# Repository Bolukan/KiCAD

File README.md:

# KiCAD
KiCad projects

## MoistureHub
To process multiple capacitive moisture sensors  
Project date: 2025-04-21  

## P1 Monitor
Multicolor leds to show home energy use  
Project date: 2024-09-29  

## W5500 RPI add-on
Add-on LAN on RPI Zero
Project date: 2024-09-29  

## SensorHub
To process multiple sensors  
Project date: 2023-06-24  

## WLED 12V ESP32
To control christmas lights with WLED  
Project date: 2022-06-07  

## ILI9341  
To combine an ILI9341 and a D1 mini. To be used with a 90 degree angle  
Project date: 2021-09-27  

## Power latching circuit  
Power latching circuit - first pcb design  
Project date: 2020-03-01

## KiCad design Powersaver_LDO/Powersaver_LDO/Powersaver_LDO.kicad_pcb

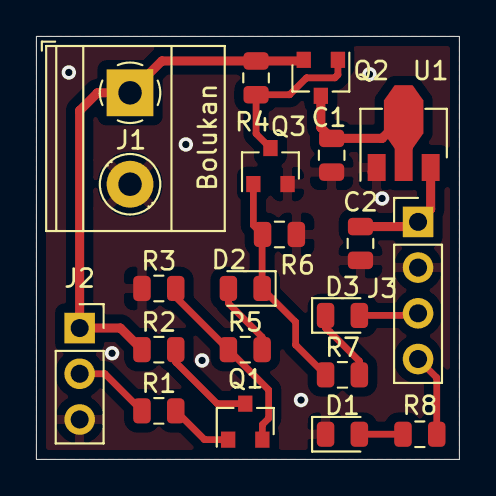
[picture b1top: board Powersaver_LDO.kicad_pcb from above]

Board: 2 copper layers, 23.5 x 23.5 mm, 20 parts (0 on the bottom side), 15 nets.

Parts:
C1, C2: 10µF; C_0805_2012Metric
D1: LED; D_0805_2012Metric
D2, D3: 1N5819W; D_0805_2012Metric
J1: Power Supply; TerminalBlock_Phoenix_MKDS-1,5-2-5.08_1x02_P5.08mm_Horizont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
J2: Trigger; PinSocket_1x03_P2.54mm_Vertical
J3: Microcontroller; PinHeader_1x04_P2.54mm_Vertical
Q1, Q3: 2N3904; SOT-23
Q2: AO3413; SOT-23
R1: 1K; R_0805_2012Metric
R2, R5: 10K; R_0805_2012Metric
R3: 220K; R_0805_2012Metric
R4, R6: 100K; R_0805_2012Metric
R7: 220; R_0805_2012Metric
R8: 330; R_0805_2012Metric
U1: HT73xx-1-SOT89; SOT-89-3

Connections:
/trigger: J2.2, R1.1
GND: C1.2, C2.2, D1.1, J1.2, J2.3, J3.2, Q3.2, R3.2, R6.2, U1.1
unnamed: C1.1, Q2.3, U1.2
unnamed: C2.1, J3.1, U1.3
unnamed: D1.2, R8.2
unnamed: D2.1, Q3.1, R6.1, R7.2
unnamed: D2.2, R5.2
unnamed: D3.1, R7.1
unnamed: D3.2, J3.3
unnamed: J3.4, R8.1
unnamed: Q1.1, R1.2
unnamed: Q1.2, R3.1, R5.1
unnamed: Q1.3, R2.2
unnamed: Q2.1, Q3.3, R4.1
VCC: J1.1, J2.1, Q2.2, R2.1, R4.2

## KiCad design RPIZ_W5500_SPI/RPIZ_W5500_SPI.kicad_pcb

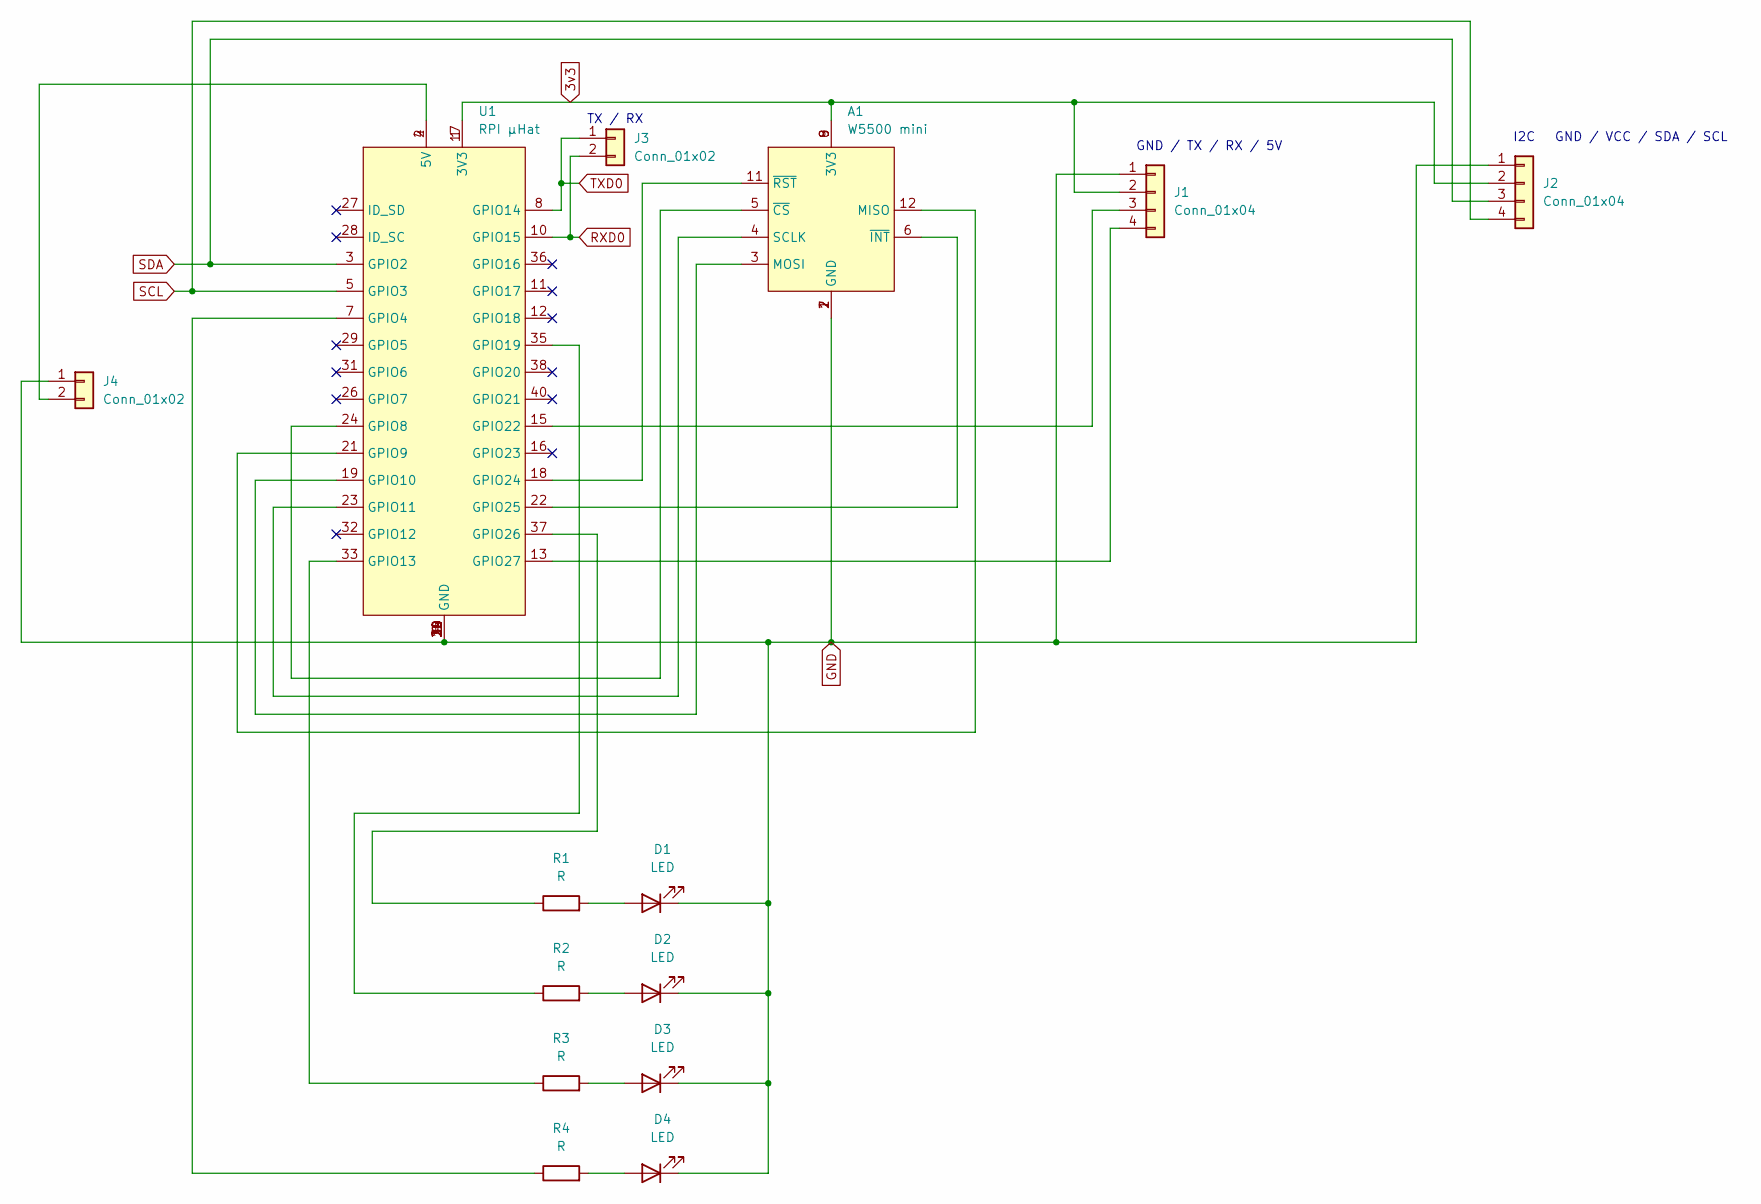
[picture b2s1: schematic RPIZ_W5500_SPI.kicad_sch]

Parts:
A1: W5500 mini; Module_W5500_mini
D1, D2, D3, D4: LED; LED_0805_2012Metric_Pad1.15x1.40mm_HandSolder
J1, J2: Conn_01x04; PinHeader_1x04_P2.54mm_Vertical
J3, J4: Conn_01x02; PinHeader_1x02_P2.54mm_Vertical
R1, R2, R3, R4: R; R_0805_2012Metric_Pad1.20x1.40mm_HandSolder
U1: RPI µHat; RPI µHat 20x2 header

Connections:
3v3: A1.8 (3V3), A1.9 (3V3), J1.2, J2.2, U1.1 (3V3), U1.17 (3V3)
GND: A1.1 (GND), A1.2 (GND), A1.7 (GND), D1.1 (K), D2.1 (K), D3.1 (K), D4.1 (K), J1.1, J2.1, J4.1, U1.6 (GND), U1.9 (GND), U1.14 (GND), U1.20 (GND), U1.25 (GND), U1.30 (GND), U1.34 (GND), U1.39 (GND)
unnamed: A1.12 (MISO), U1.21 (GPIO9)
unnamed: A1.3 (MOSI), U1.19 (GPIO10)
unnamed: A1.4 (SCLK), U1.23 (GPIO11)
unnamed: A1.5 (~CS), U1.24 (GPIO8)
unnamed: A1.6 (~INT), U1.22 (GPIO25)
unnamed: A1.11 (~RST), U1.18 (GPIO24)
unnamed: D1.2 (A), R1.2
unnamed: D2.2 (A), R2.2
unnamed: D3.2 (A), R3.2
unnamed: D4.2 (A), R4.2
unnamed: J1.3, U1.15 (GPIO22)
unnamed: J1.4, U1.13 (GPIO27)
unnamed: J4.2, U1.2 (5V), U1.4 (5V)
unnamed: R4.1, U1.7 (GPIO4)
unnamed: R3.1, U1.33 (GPIO13)
unnamed: R2.1, U1.35 (GPIO19)
unnamed: R1.1, U1.37 (GPIO26)
RXD0: J3.2, U1.10 (GPIO15)
SCL: J2.4, U1.5 (GPIO3)
SDA: J2.3, U1.3 (GPIO2)
TXD0: J3.1, U1.8 (GPIO14)

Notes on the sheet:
GND / TX / RX / 5V
I2C
GND / VCC / SDA / SCL
TX / RX

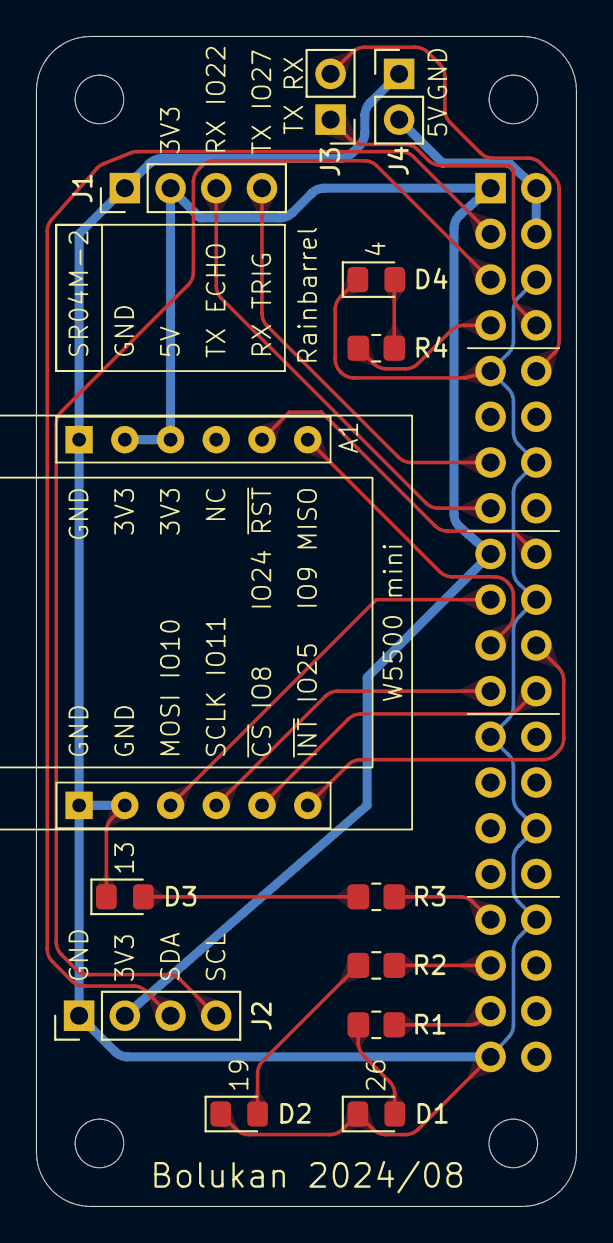
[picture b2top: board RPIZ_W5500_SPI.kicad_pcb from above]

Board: 2 copper layers, 30.0 x 65.0 mm, 14 parts (0 on the bottom side), 23 nets.

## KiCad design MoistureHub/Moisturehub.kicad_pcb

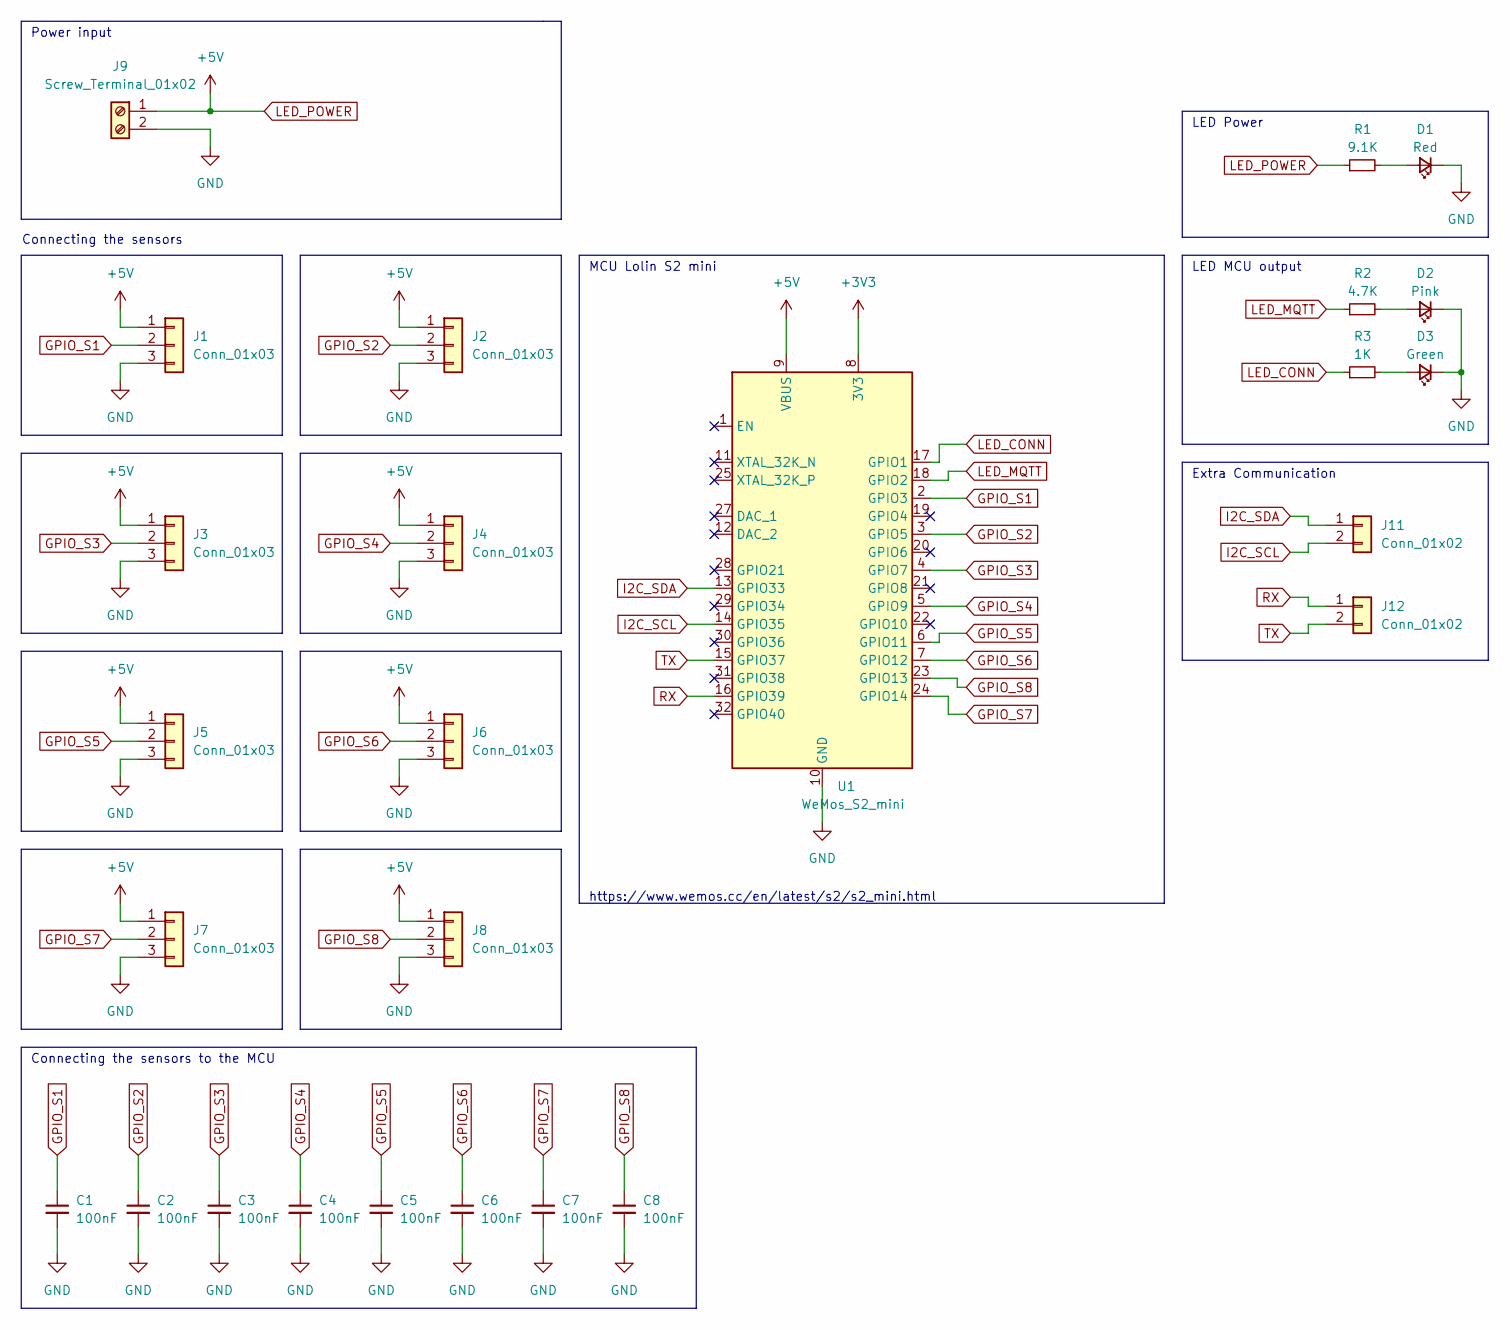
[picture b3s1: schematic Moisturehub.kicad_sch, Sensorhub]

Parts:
C1, C2, C3, C4, C5, C6, C7, C8: 100nF; C_1206_3216Metric_Pad1.33x1.80mm_HandSolder
D1: Red; LED_1206_3216Metric_Pad1.42x1.75mm_HandSolder
D2: Pink; LED_1206_3216Metric_Pad1.42x1.75mm_HandSolder
D3: Green; LED_1206_3216Metric_Pad1.42x1.75mm_HandSolder
J1, J2, J3, J4, J5, J6, J7, J8: Conn_01x03; JST_XH_S3B-XH-A_1x03_P2.50mm_Horizontal
J9: Screw_Terminal_01x02; TerminalBlock_Phoenix_MKDS-1,5-2-5.08_1x02_P5.08mm_Horizont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
J11, J12: Conn_01x02; PinHeader_1x02_P2.54mm_Vertical
R1: 9.1K; R_1206_3216Metric_Pad1.30x1.75mm_HandSolder
R2: 4.7K; R_1206_3216Metric_Pad1.30x1.75mm_HandSolder
R3: 1K; R_1206_3216Metric_Pad1.30x1.75mm_HandSolder
U1: WeMos_S2_mini; WEMOS_S2_mini

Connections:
+3V3: U1.8 (3V3)
GND: C1.2, C2.2, C3.2, C4.2, C5.2, C6.2, C7.2, C8.2, D1.1 (K), D2.1 (K), D3.1 (K), J1.3, J2.3, J3.3, J4.3, J5.3, J6.3, J7.3, J8.3, J9.2, U1.10 (GND), U1.26 (GND)
GPIO_S1: C1.1, J1.2, U1.2 (GPIO3)
GPIO_S2: C2.1, J2.2, U1.3 (GPIO5)
GPIO_S3: C3.1, J3.2, U1.4 (GPIO7)
GPIO_S4: C4.1, J4.2, U1.5 (GPIO9)
GPIO_S5: C5.1, J5.2, U1.6 (GPIO11)
GPIO_S6: C6.1, J6.2, U1.7 (GPIO12)
GPIO_S7: C7.1, J7.2, U1.24 (GPIO14)
GPIO_S8: C8.1, J8.2, U1.23 (GPIO13)
I2C_SCL: J11.2, U1.14 (GPIO35)
I2C_SDA: J11.1, U1.13 (GPIO33)
LED_CONN: R3.1, U1.17 (GPIO1)
LED_MQTT: R2.1, U1.18 (GPIO2)
LED_POWER: J1.1, J2.1, J3.1, J4.1, J5.1, J6.1, J7.1, J8.1, J9.1, R1.1, U1.9 (VBUS)
unnamed: D1.2 (A), R1.2
unnamed: D2.2 (A), R2.2
unnamed: D3.2 (A), R3.2
RX: J12.1, U1.16 (GPIO39)
TX: J12.2, U1.15 (GPIO37)

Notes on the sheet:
Extra Communication
Connecting the sensors to the MCU
LED Power
Power input
https://www.wemos.cc/en/latest/s2/s2_mini.html
Connecting the sensors
MCU Lolin S2 mini
LED MCU output

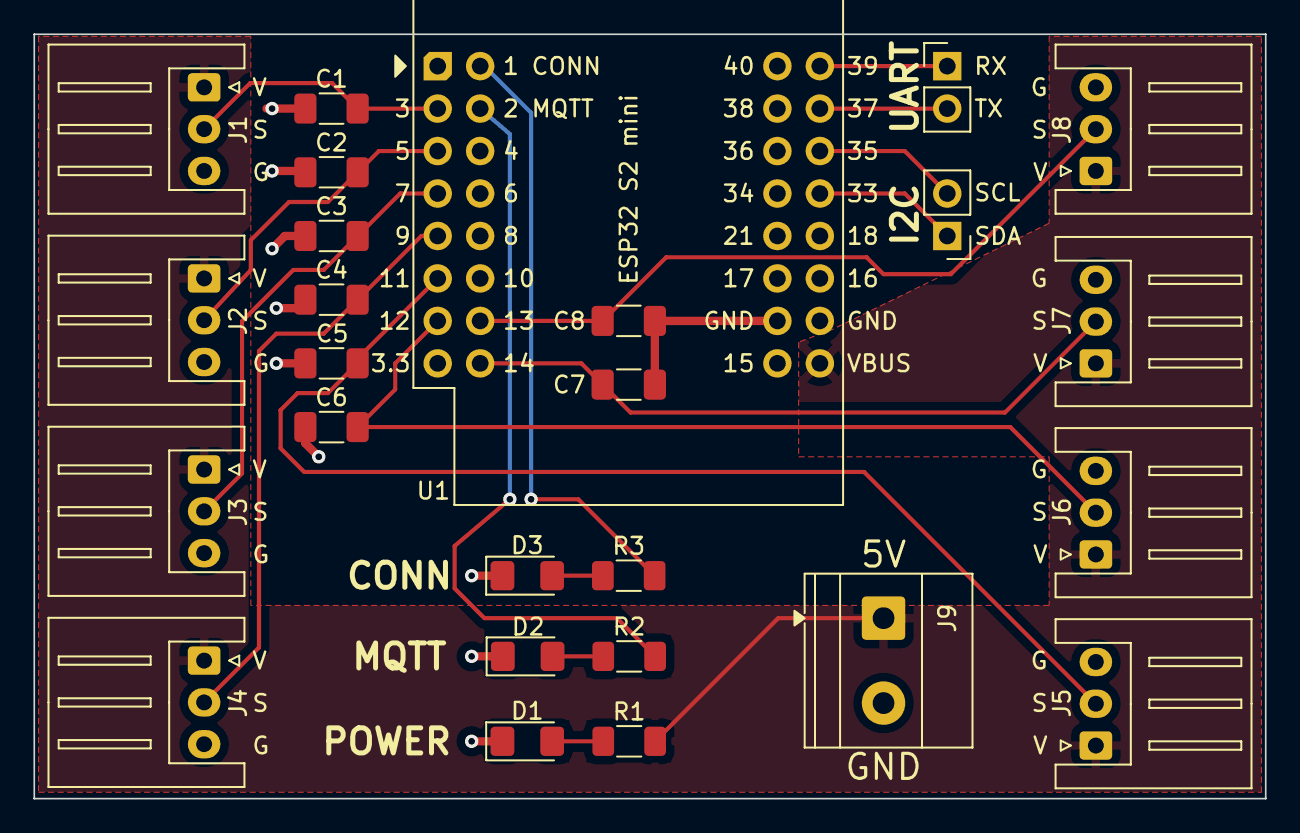
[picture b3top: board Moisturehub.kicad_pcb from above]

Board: 2 copper layers, 73.7 x 45.7 mm, 26 parts (0 on the bottom side), 19 nets.

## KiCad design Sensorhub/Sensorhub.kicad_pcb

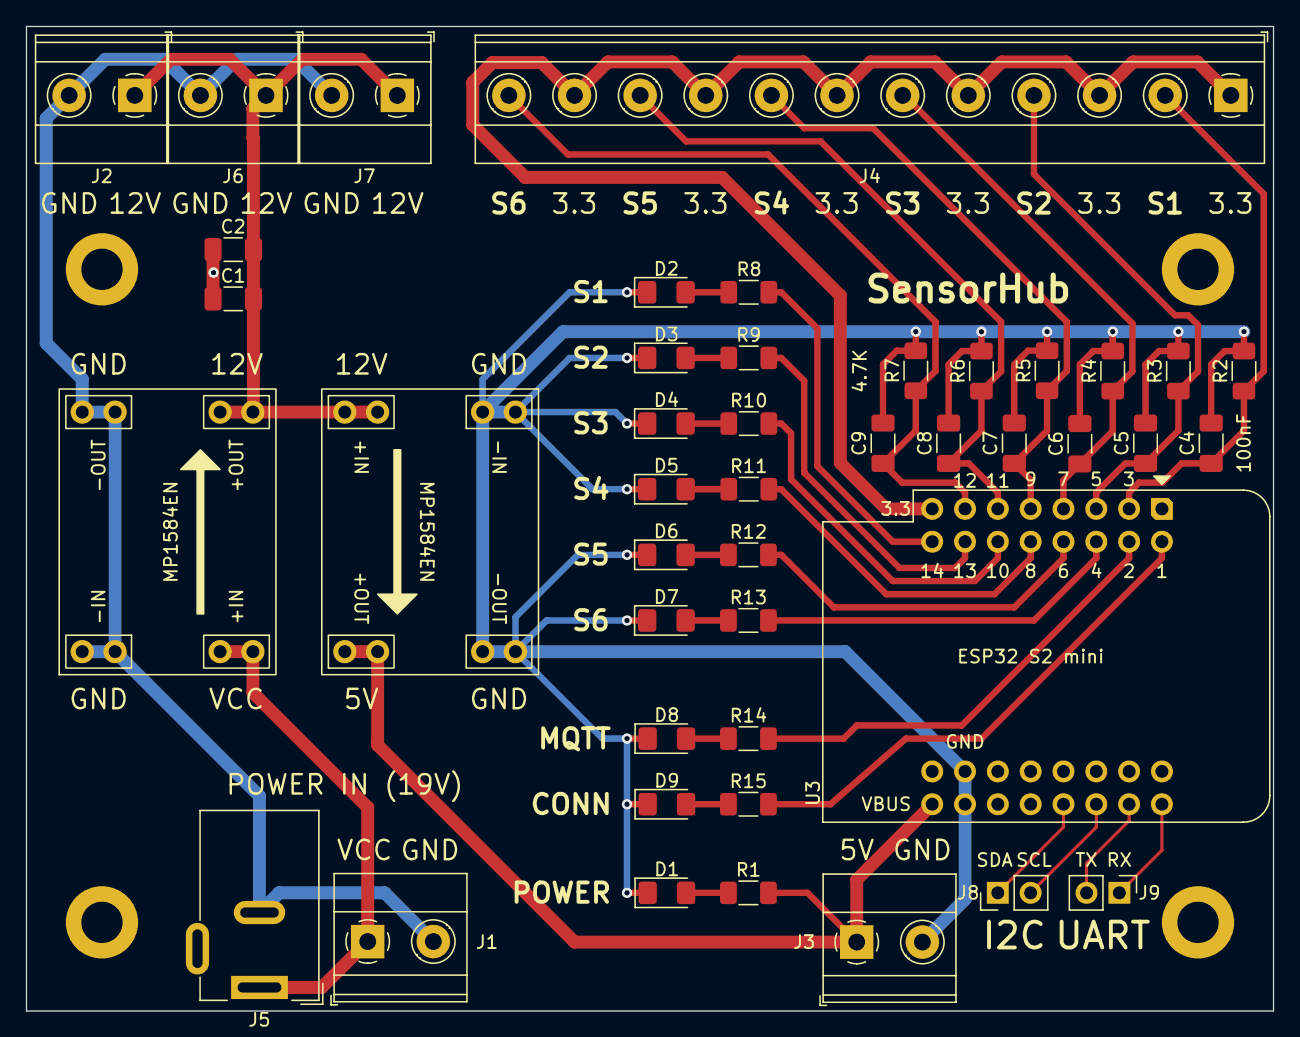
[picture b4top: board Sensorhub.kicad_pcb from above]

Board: 2 copper layers, 96.5 x 76.2 mm, 48 parts (0 on the bottom side), 32 nets.

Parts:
C1, C2, C4, C5, C6, C7, C8, C9: 100nF; C_1206_3216Metric_Pad1.33x1.80mm_HandSolder
D1: Red; LED_1206_3216Metric_Pad1.42x1.75mm_HandSolder
D2, D3, D4, D5, D6, D7: Blue; LED_1206_3216Metric_Pad1.42x1.75mm_HandSolder
D8, D9: Pink; LED_1206_3216Metric_Pad1.42x1.75mm_HandSolder
H1, H2, H3, H4: MountingHole; MountingHole_3.2mm_M3_DIN965_Pad
J1, J2, J3, J6, J7: Screw_Terminal_01x02; TerminalBlock_Phoenix_MKDS-1,5-2-5.08_1x02_P5.08mm_Horizont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
J4: Screw_Terminal_01x12; TerminalBlock_Phoenix_MKDS-1,5-12-5.08_1x12_P5.08mm_Horizon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
J5: Barrel_Jack; BarrelJack_Wuerth_6941xx301002
J8, J9: Conn_01x02; PinHeader_1x02_P2.54mm_Vertical
R1, R8, R9, R10, R11, R12, R13, R14, R15: 1K; R_1206_3216Metric_Pad1.30x1.75mm_HandSolder
R2, R3, R4, R5, R6, R7: 4.7K; R_1206_3216Metric_Pad1.30x1.75mm_HandSolder
U1: MP1584EN-12V; MP1584EN_PCB
U2: MP1584EN-5V; MP1584EN_PCB
U3: WeMos_S2_mini; WEMOS_S2_mini

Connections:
+3V3: J4.1, J4.3, J4.5, J4.7, J4.9, J4.11, U3.8 (3V3)
+5V: J3.1, R1.1, U2.4 (OUT+), U3.9 (VBUS)
+12V: C1.1, C2.1, J2.1, J6.1, J7.1, U1.4 (OUT+), U2.2 (IN+)
GND: C1.2, C2.2, C4.2, C5.2, C6.2, C7.2, C8.2, C9.2, D1.1 (K), D2.1 (K), D3.1 (K), D4.1 (K), D5.1 (K), D6.1 (K), D7.1 (K), D8.1 (K), D9.1 (K), J1.2, J2.2, J3.2, J5.2, J6.2, J7.2, R2.2, R3.2, R4.2, R5.2, R6.2, R7.2, U1.1 (IN-), U1.3 (OUT-), U2.1 (IN-), U2.3 (OUT-), U3.10 (GND), U3.26 (GND)
GPIO_LED1: R8.1, U3.24 (GPIO14)
GPIO_LED2: R9.1, U3.23 (GPIO13)
GPIO_LED3: R10.1, U3.22 (GPIO10)
GPIO_LED4: R11.1, U3.21 (GPIO8)
GPIO_LED5: R12.1, U3.20 (GPIO6)
GPIO_LED6: R13.1, U3.19 (GPIO4)
GPIO_LED_B: R15.1, U3.17 (GPIO1)
GPIO_LED_MQTT: R14.1, U3.18 (GPIO2)
GPIO_S1: C4.1, J4.2, R2.1, U3.2 (GPIO3)
GPIO_S2: C5.1, J4.4, R3.1, U3.3 (GPIO5)
GPIO_S3: C6.1, J4.6, R4.1, U3.4 (GPIO7)
GPIO_S4: C7.1, J4.8, R5.1, U3.5 (GPIO9)
GPIO_S5: C8.1, J4.10, R6.1, U3.6 (GPIO11)
GPIO_S6: C9.1, J4.12, R7.1, U3.7 (GPIO12)
I2C_SCL: J8.2, U3.14 (GPIO35)
I2C_SDA: J8.1, U3.13 (GPIO33)
unnamed: D1.2 (A), R1.2
unnamed: D2.2 (A), R8.2
unnamed: D3.2 (A), R9.2
unnamed: D4.2 (A), R10.2
unnamed: D5.2 (A), R11.2
unnamed: D6.2 (A), R12.2
unnamed: D7.2 (A), R13.2
unnamed: D8.2 (A), R14.2
unnamed: D9.2 (A), R15.2
RX: J9.1, U3.16 (GPIO39)
TX: J9.2, U3.15 (GPIO37)
VCC: J1.1, J5.1, U1.2 (IN+)

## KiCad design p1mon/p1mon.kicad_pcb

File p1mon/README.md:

## P1 Monitor
Multicolor leds to show home energy use  
Project date: 2024-09-29

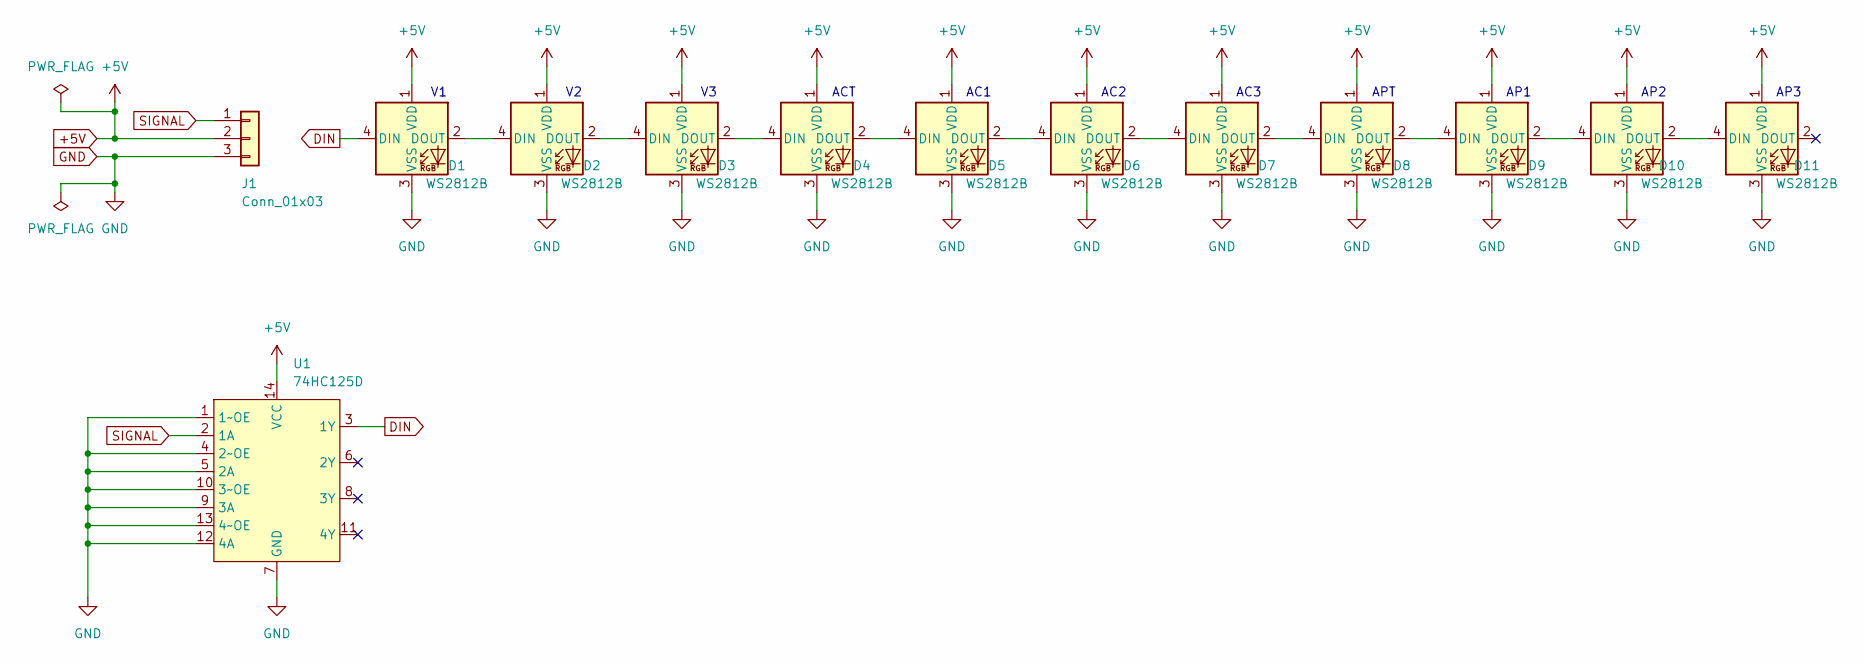
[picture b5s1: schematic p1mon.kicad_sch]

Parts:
D1, D2, D3, D4, D5, D6, D7, D8, D9, D10, D11: WS2812B; LED_WS2812B_PLCC4_5.0x5.0mm_P3.2mm
J1: Conn_01x03; PinHeader_1x03_P2.54mm_Vertical
U1: 74HC125D; SOP-14_3.9x8.65mm_P1.27mm

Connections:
+5V: D1.1 (VDD), D2.1 (VDD), D3.1 (VDD), D4.1 (VDD), D5.1 (VDD), D6.1 (VDD), D7.1 (VDD), D8.1 (VDD), D9.1 (VDD), D10.1 (VDD), D11.1 (VDD), J1.2, U1.14 (VCC)
DIN: D1.4 (DIN), U1.3 (1Y)
GND: D1.3 (VSS), D2.3 (VSS), D3.3 (VSS), D4.3 (VSS), D5.3 (VSS), D6.3 (VSS), D7.3 (VSS), D8.3 (VSS), D9.3 (VSS), D10.3 (VSS), D11.3 (VSS), J1.3, U1.1 (1~OE), U1.4 (2~OE), U1.5 (2A), U1.7 (GND), U1.9 (3A), U1.10 (3~OE), U1.12 (4A), U1.13 (4~OE)
unnamed: D1.2 (DOUT), D2.4 (DIN)
unnamed: D2.2 (DOUT), D3.4 (DIN)
unnamed: D3.2 (DOUT), D4.4 (DIN)
unnamed: D4.2 (DOUT), D5.4 (DIN)
unnamed: D5.2 (DOUT), D6.4 (DIN)
unnamed: D6.2 (DOUT), D7.4 (DIN)
unnamed: D7.2 (DOUT), D8.4 (DIN)
unnamed: D8.2 (DOUT), D9.4 (DIN)
unnamed: D9.2 (DOUT), D10.4 (DIN)
unnamed: D10.2 (DOUT), D11.4 (DIN)
SIGNAL: J1.1, U1.2 (1A)

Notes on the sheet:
AC2
APT
AP1
ACT
AP2
AC3
AP3
AC1

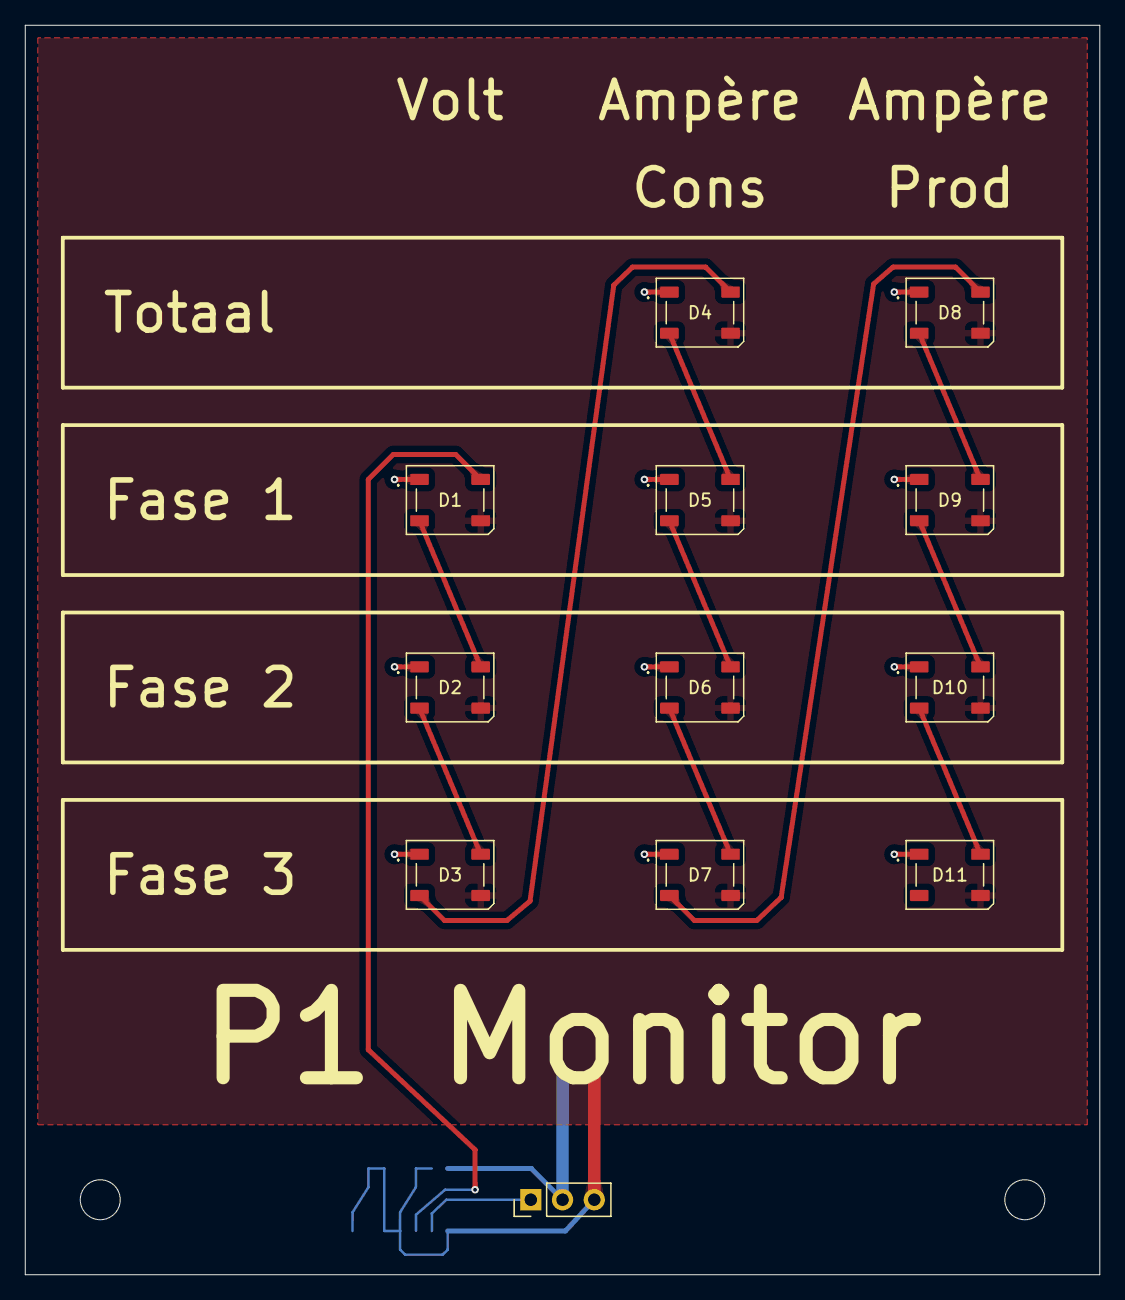
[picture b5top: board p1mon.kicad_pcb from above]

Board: 2 copper layers, 86.0 x 100.0 mm, 13 parts (1 on the bottom side), 14 nets.

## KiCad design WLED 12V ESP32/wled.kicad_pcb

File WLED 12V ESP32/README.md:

## WLED 12V ESP32
To control christmas lights with WLED  
Project date: 2022-06-07

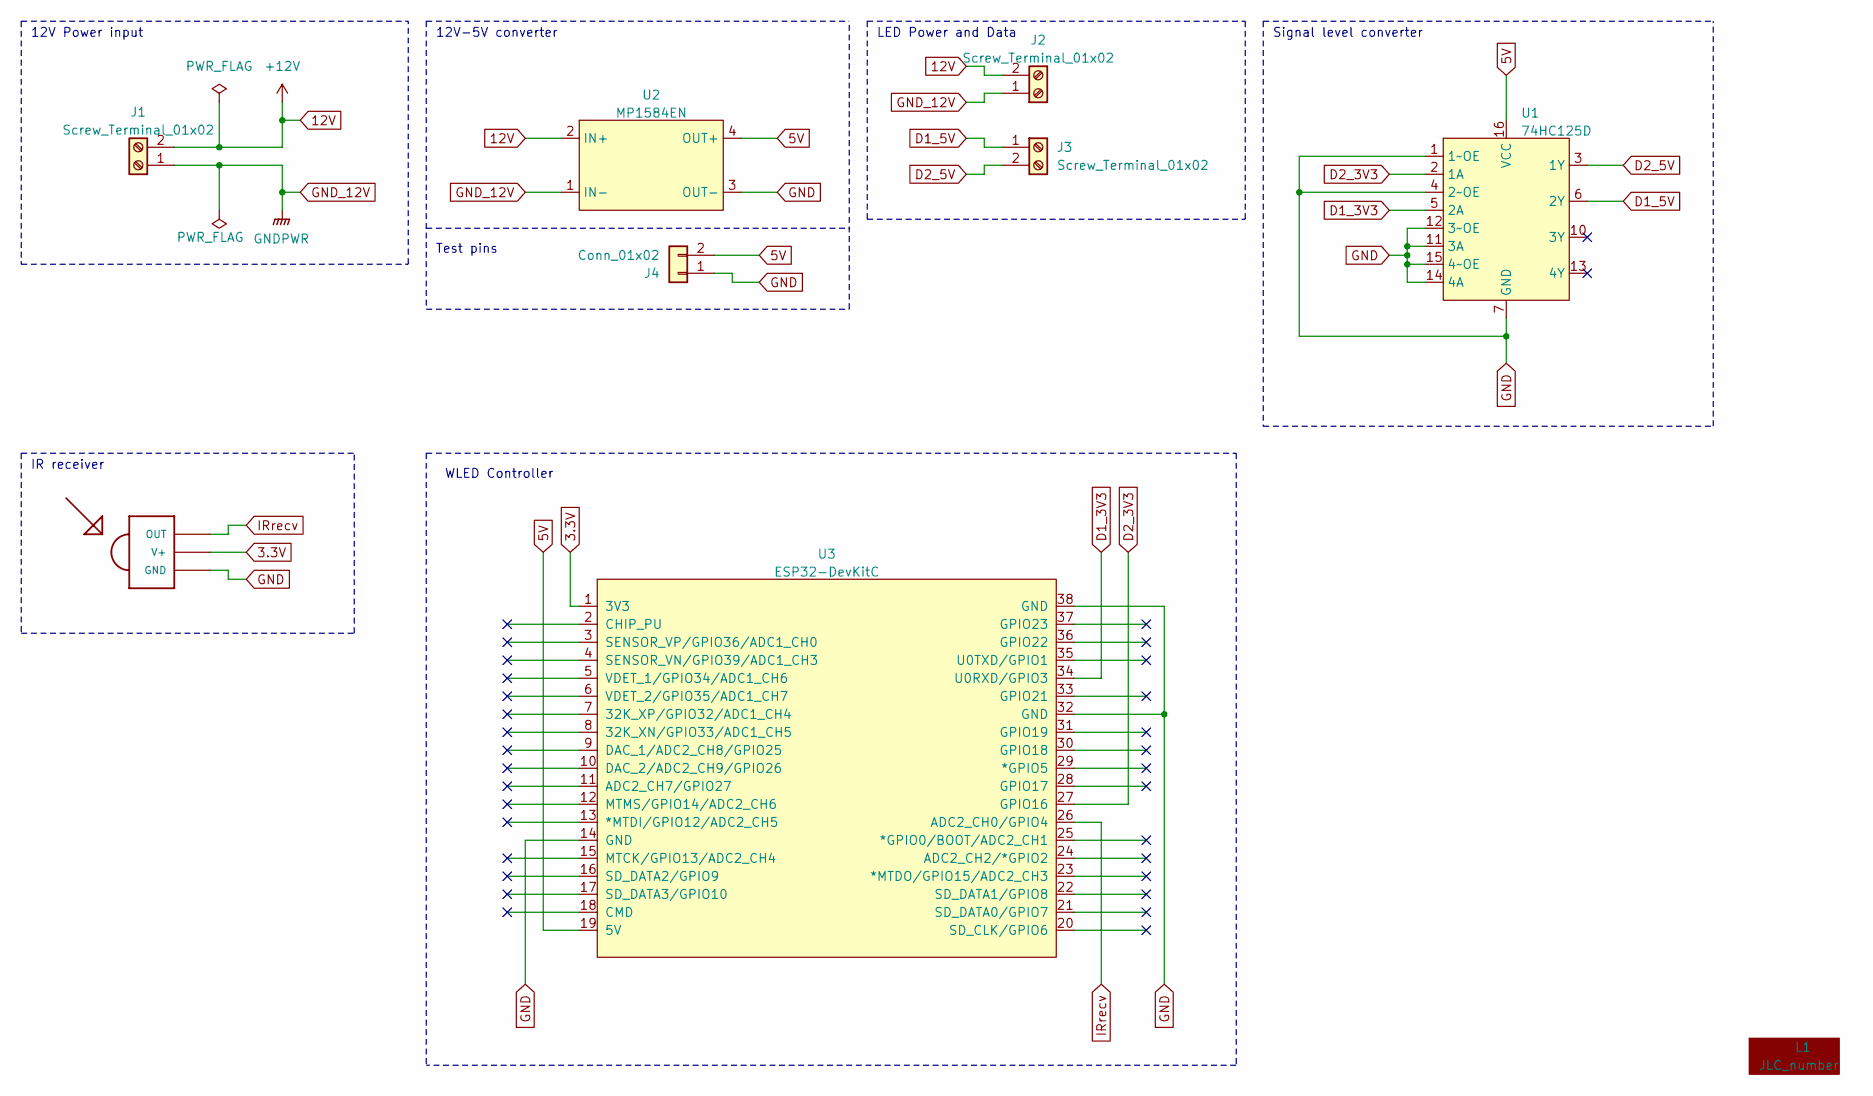
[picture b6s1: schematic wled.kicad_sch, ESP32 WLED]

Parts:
J1, J2, J3: Screw_Terminal_01x02; TerminalBlock_Phoenix_MKDS-1,5-2-5.08_1x02_P5.08mm_Horizont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
J4: Conn_01x02; PinHeader_1x02_P2.54mm_Vertical
L1: JLC_number; JLC number
U1: 74HC125D; HCT125 - SOPDIP-16_W12.7mm
U2: MP1584EN; MP1584EN_PCB
U3: ESP32-DevKitC
U4: TSOP1838; TSOP18XX

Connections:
3.3V: U3.1 (3V3), U4.VCC (V+)
5V: J4.2, U1.16 (VCC), U2.4 (OUT+), U3.19 (5V)
12V: J1.2, J2.2, U2.2 (IN+)
D1_3V3: U1.5 (2A), U3.34 (U0RXD/GPIO3)
D1_5V: J3.1, U1.6 (2Y)
D2_3V3: U1.2 (1A), U3.27 (GPIO16)
D2_5V: J3.2, U1.3 (1Y)
GND: J4.1, U1.1 (1~OE), U1.4 (2~OE), U1.7 (GND), U1.11 (3A), U1.12 (3~OE), U1.14 (4A), U1.15 (4~OE), U2.3 (OUT-), U3.14 (GND), U3.32 (GND), U3.38 (GND), U4.GND
GND_12V: J1.1, J2.1, U2.1 (IN-)
IRrecv: U3.26 (ADC2_CH0/GPIO4), U4.OUT

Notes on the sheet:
12V Power input
Signal level converter
LED Power and Data
IR receiver
Test pins
12V-5V converter
WLED Controller

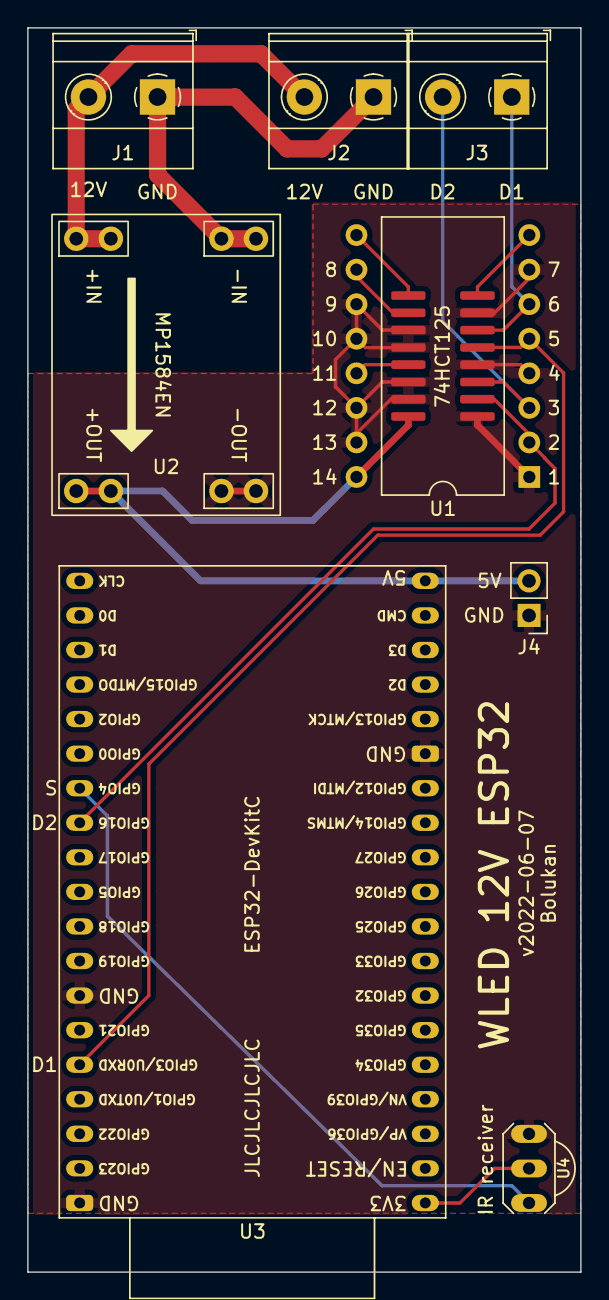
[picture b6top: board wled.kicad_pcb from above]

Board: 2 copper layers, 40.6 x 91.4 mm, 9 parts (0 on the bottom side), 10 nets.

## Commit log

2021-09-30 Add project ili9341 v2021-09-27
2021-09-30 Add images of ili9241 pcb
2021-09-30 Add schematic ili9341
2026-05-13 Update images
2026-05-13 Add WLED 12V ESP32
2026-05-13 Adjust images
2026-05-13 Add P1 monitor
2026-05-13 Add local readme's
2026-05-13 Add p1mon kicad files
2026-05-13 Add Moisturehub and Sensorhub
2026-05-13 Add RPIZ W5500
2026-05-13 Smaller images
2026-05-13 Add Powersaver
2026-05-13 Add images
2026-05-13 Powersaver kicad files
